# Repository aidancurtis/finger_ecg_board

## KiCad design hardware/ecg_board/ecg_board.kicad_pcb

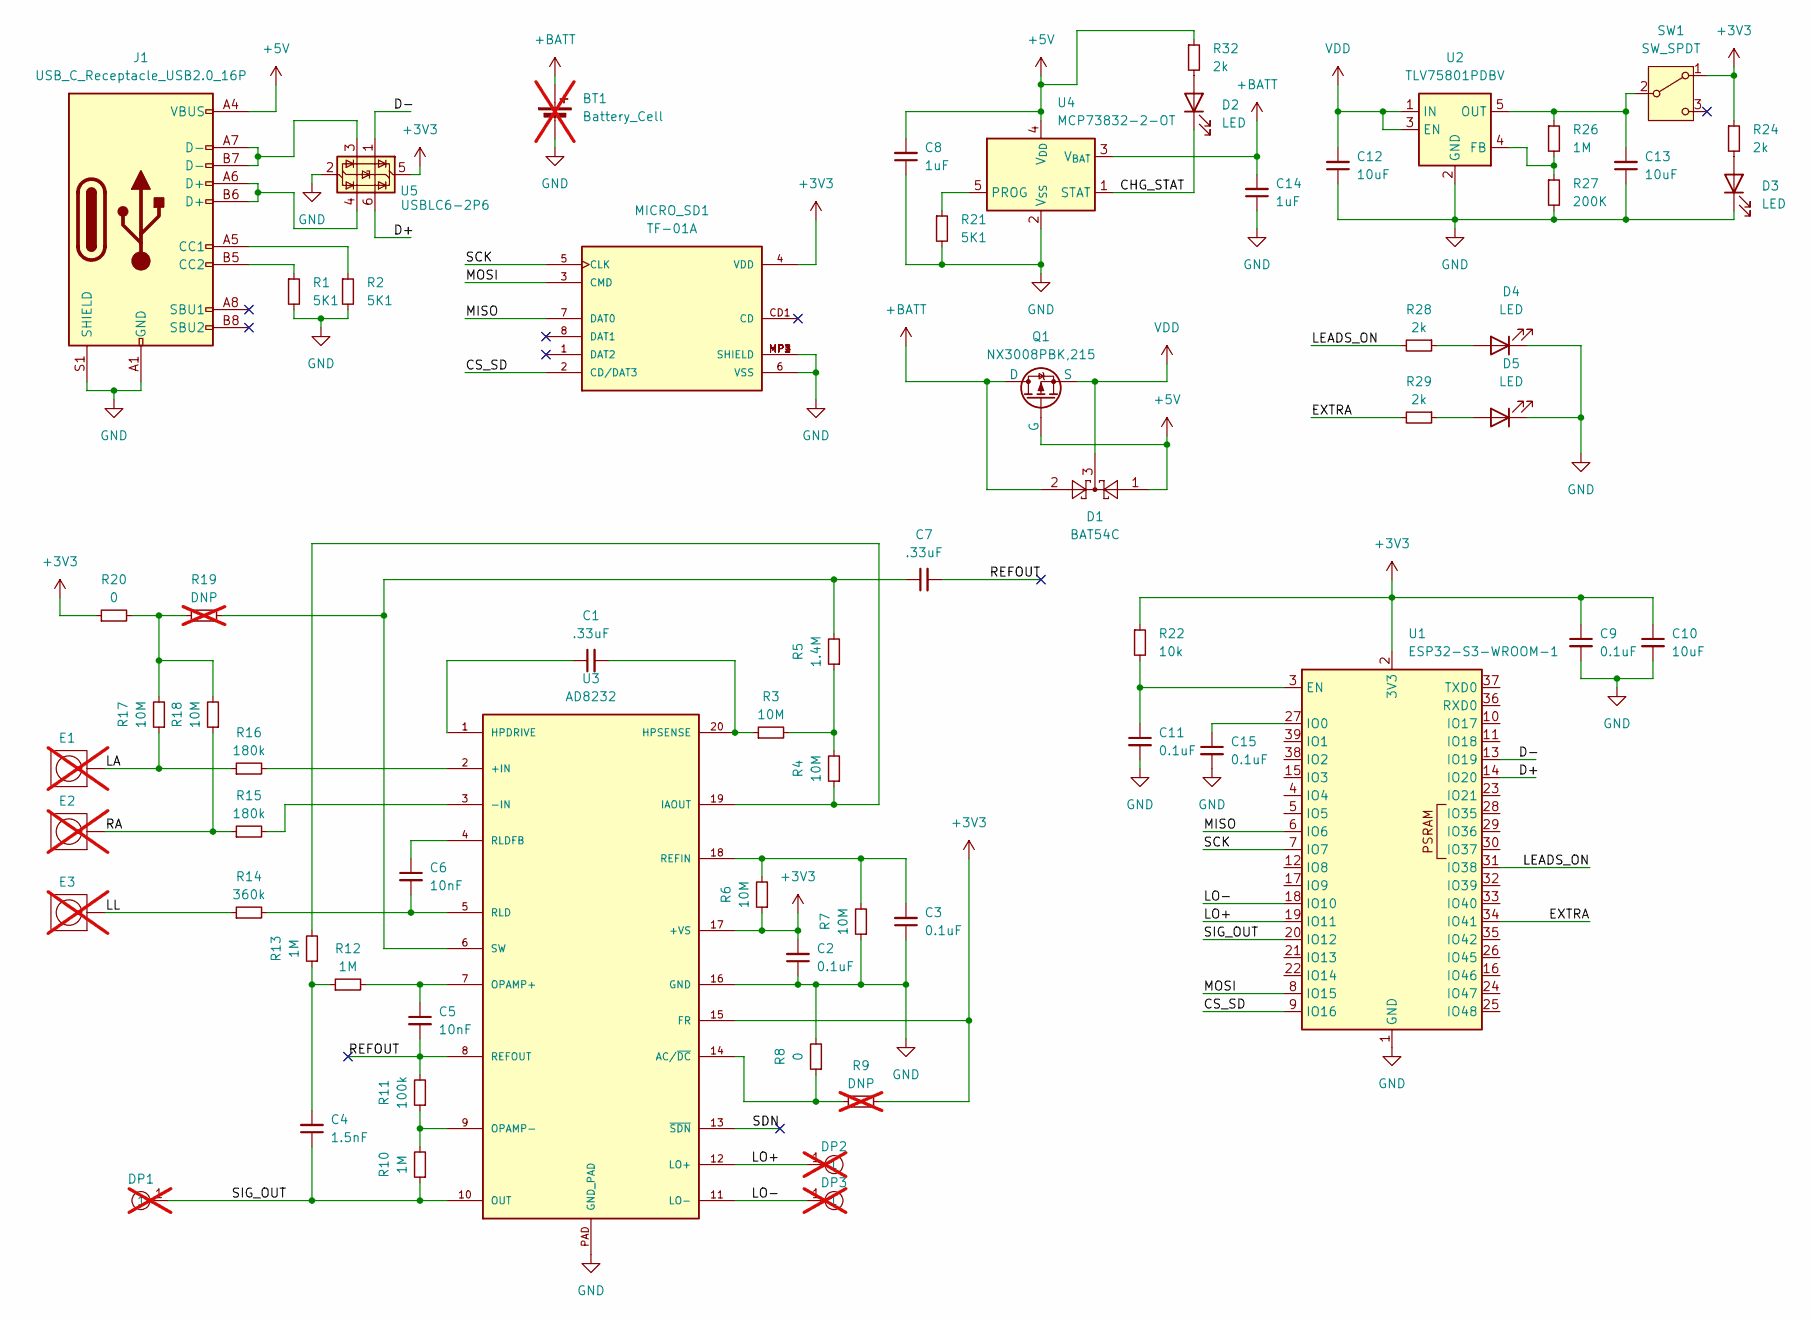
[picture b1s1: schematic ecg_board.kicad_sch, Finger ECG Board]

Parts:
BT1: Battery_Cell; battery_pads; not fitted
C1, C7: .33uF; C_0603_1608Metric; LCSC Part # C2991452
C2, C3, C9, C11, C15: 0.1uF; C_0603_1608Metric; LCSC Part # C14663
C4: 1.5nF; C_0603_1608Metric; LCSC Part # C1588
C5, C6: 10nF; C_0603_1608Metric; LCSC Part # C57112
C8, C14: 1uF; C_0603_1608Metric; LCSC Part # C15849
C10, C12, C13: 10uF; C_0805_2012Metric; LCSC Part # C19702
D1: BAT54C; SOT-23; LCSC Part # C2828464
D2, D3, D4: LED; LED_0603_1608Metric; LCSC Part # C2286
D5: LED; LED_0603_1608Metric; LCSC Part # C5123548
DP1, DP2, DP3: DebugPad; not fitted
E1, E2, E3: Finger_Electrode; not fitted
J1: USB_C_Receptacle_USB2.0_16P; USB_C_Receptacle_HCTL_HC-TYPE-C-16P-01A; LCSC Part # C2927038
MICRO_SD1: TF-01A; LCSC Part # C2889258
Q1: NX3008PBK,215; SOT-23-3; LCSC Part # C131670
R1, R2, R21: 5K1; R_0603_1608Metric; LCSC Part # C23186
R3, R4, R6, R7, R17, R18: 10M; R_0603_1608Metric; LCSC Part # C7250
R5: 1.4M; R_0603_1608Metric; LCSC Part # C3016282
R8, R20: 0; R_0603_1608Metric; LCSC Part # C21189
R9, R19: DNP; R_0603_1608Metric; not fitted
R10, R12, R13, R26: 1M; R_0603_1608Metric; LCSC Part # C22935
R11: 100k; R_0603_1608Metric; LCSC Part # C25803
R14: 360k; R_0603_1608Metric; LCSC Part # C3016408
R15, R16: 180k; R_0603_1608Metric; LCSC Part # C325602
R22: 10k; R_0603_1608Metric; LCSC Part # C25804
R24, R28, R29, R32: 2k; R_0603_1608Metric; LCSC Part # C22975
R27: 200K; R_0603_1608Metric; LCSC Part # C25811
SW1: SW_SPDT; SW_SPDT_PCM12; LCSC Part # C109335
U1: ESP32-S3-WROOM-1; LCSC Part # C2913197
U2: TLV75801PDBV; SOT-23-5; LCSC Part # C2877852
U3: AD8232; LFCSP_20; LCSC Part # C43216
U4: MCP73832-2-OT; SOT-23-5; LCSC Part # C38066
U5: USBLC6-2P6; SOT-666; LCSC Part # C2827693

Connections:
+3V3: C2.2, C9.1, C10.1, MICRO_SD1.4 (VDD), R6.1, R9.2, R20.1, R22.1, R24.1, SW1.1 (A), U1.2 (3V3), U3.15 (FR), U3.17 (+VS), U5.5 (VBUS)
+5V: C8.2, D1.1, J1.A4 (VBUS), J1.A9 (VBUS), J1.B4 (VBUS), J1.B9 (VBUS), Q1.2 (G), R32.1, U4.4 (V_{DD})
+BATT: BT1.1 (+), C14.2, D1.2, Q1.1 (D), U4.3 (V_{BAT})
/CHG_STAT: D2.1 (K), U4.1 (STAT)
/CS_SD: MICRO_SD1.2 (CD/DAT3), U1.9 (IO16)
/D+: U1.14 (IO20), U5.6 (I/O1)
/D-: U1.13 (IO19), U5.1 (I/O1)
/EXTRA: R29.2, U1.34 (IO41)
/LA: E1.1, R16.1, R17.1
/LEADS_ON: R28.2, U1.31 (IO38)
/LL: E3.1, R14.1
/LO+: DP2.1, U1.19 (IO11), U3.12 (LO+); also elsewhere on the board
/LO-: DP3.1, U1.18 (IO10), U3.11 (LO-); also elsewhere on the board
/MISO: MICRO_SD1.7 (DAT0), U1.6 (IO6)
/MOSI: MICRO_SD1.3 (CMD), U1.8 (IO15)
/RA: E2.1, R15.1, R18.1
/REFOUT: C5.2, C7.2, R11.2, U3.8 (REFOUT)
/SCK: MICRO_SD1.5 (CLK), U1.7 (IO7)
/SDN: U3.13 (~SDN)
/SIG_OUT: C4.1, DP1.1, R10.1, U1.20 (IO12), U3.10 (OUT); also elsewhere on the board
GND: BT1.2 (-), C2.1, C3.1, C8.1, C9.2, C10.2, C11.2, C12.1, C13.1, C14.1, C15.2, D3.1 (K), D4.1 (K), D5.1 (K), J1.A1 (GND), J1.A12 (GND), J1.B1 (GND), J1.B12 (GND), J1.S1 (SHIELD), MICRO_SD1.6 (VSS), MICRO_SD1.MP1 (SHIELD), MICRO_SD1.MP2 (SHIELD), MICRO_SD1.MP3 (SHIELD), MICRO_SD1.MP4 (SHIELD), R1.2, R2.2, R7.1, R8.2, R21.2, R27.2, U1.1 (GND), U1.40 (GND), U1.41 (GND), U2.2 (GND), U3.16 (GND), U3.PAD (GND_PAD), U4.2 (V_{SS}), U5.2 (GND)
unnamed: C4.2, R12.1, R13.1
unnamed: D2.2 (A), R32.2
unnamed: D3.2 (A), R24.2
unnamed: D4.2 (A), R28.1
unnamed: D5.2 (A), R29.1
unnamed: J1.A5 (CC1), R2.1
unnamed: J1.B5 (CC2), R1.1
unnamed: J1.A6 (D+), J1.B6 (D+), U5.4 (I/O2)
unnamed: J1.A7 (D-), J1.B7 (D-), U5.3 (I/O2)
unnamed: R3.2, R4.2, R5.1
unnamed: R17.2, R18.2, R19.1, R20.2
unnamed: C13.2, R26.1, SW1.2 (B), U2.5 (OUT)
unnamed: C11.1, R22.2, U1.3 (EN)
unnamed: C15.1, U1.27 (IO0)
unnamed: R26.2, R27.1, U2.4 (FB)
unnamed: R16.2, U3.2 (+IN)
unnamed: R15.2, U3.3 (-IN)
unnamed: R8.1, R9.1, U3.14 (AC/~DC)
unnamed 39: C1.1, U3.1 (HPDRIVE); also elsewhere on the board
unnamed 40: C1.2, R3.1, U3.20 (HPSENSE); also elsewhere on the board
unnamed: R4.1, R13.2, U3.19 (IAOUT)
unnamed: C5.1, R12.2, U3.7 (OPAMP+)
unnamed: R10.2, R11.1, U3.9 (OPAMP-)
unnamed: C3.2, R6.2, R7.2, U3.18 (REFIN)
unnamed: C6.2, R14.2, U3.5 (RLD)
unnamed: C6.1, U3.4 (RLDFB)
unnamed: C7.1, R5.2, R19.2, U3.6 (SW)
unnamed: R21.1, U4.5 (PROG)
VDD: C12.2, D1.3, Q1.3 (S), U2.1 (IN), U2.3 (EN)

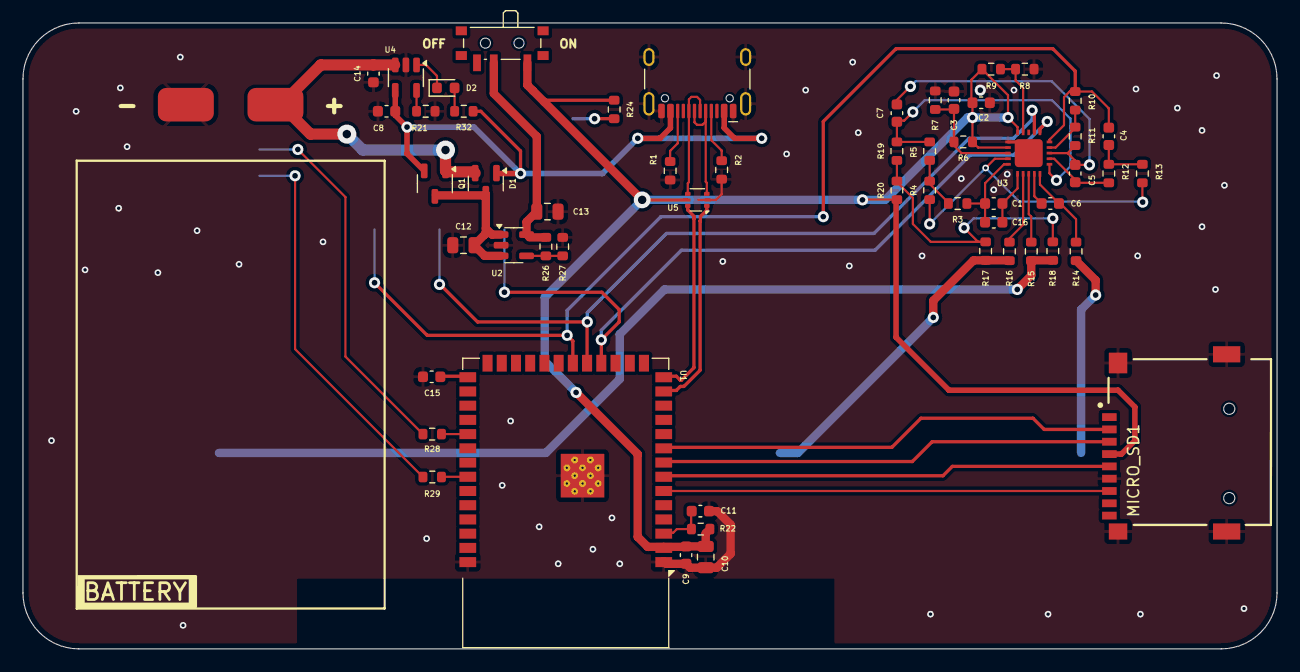
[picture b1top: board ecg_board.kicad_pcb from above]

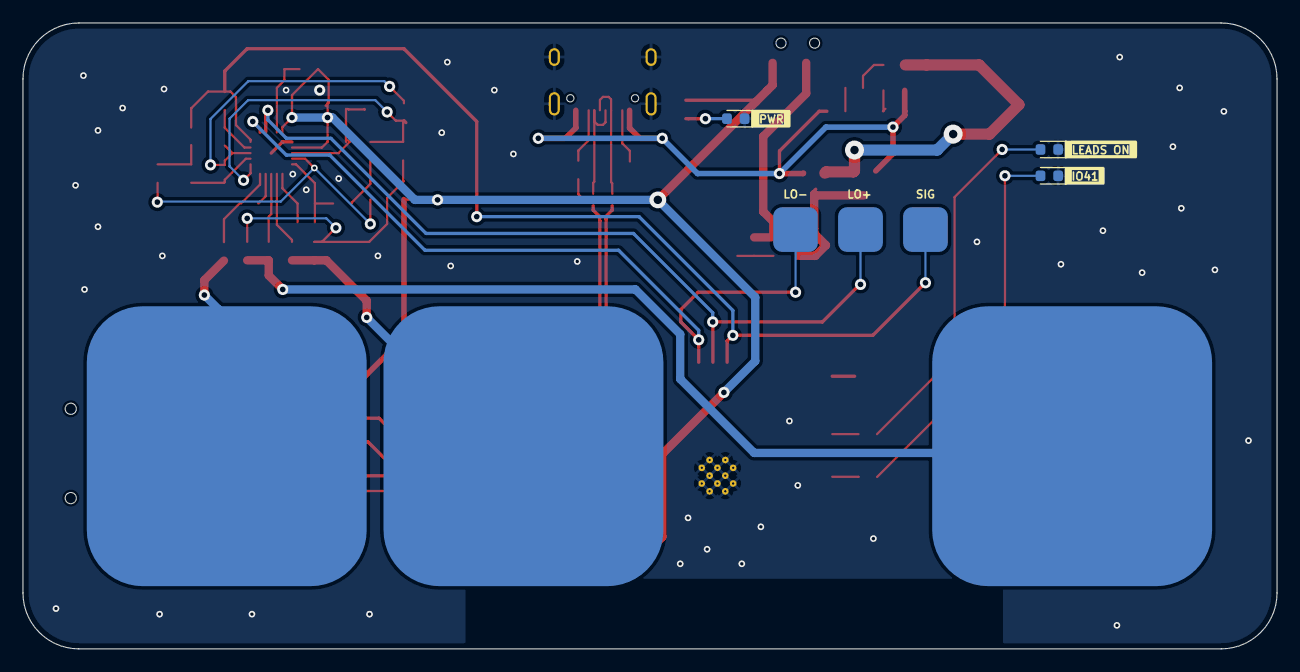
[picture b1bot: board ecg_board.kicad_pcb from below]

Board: 2 copper layers, 112.0 x 55.9 mm, 65 parts (9 on the bottom side), 49 nets.

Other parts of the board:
C16: 220nF; C_0603_1608Metric
LO+: DebugPad
LO-: DebugPad
SIG: DebugPad

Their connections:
/LO+: LO+.1; also elsewhere on the board
/LO-: LO-.1; also elsewhere on the board
/SIG_OUT: SIG.1; also elsewhere on the board
unnamed 39: C16.1; also elsewhere on the board
unnamed 40: C16.2; also elsewhere on the board

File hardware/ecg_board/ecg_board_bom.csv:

"Reference","Value","Datasheet","Footprint","Qty","DNP","LCSC Part #"
"C1",".33uF","~","Capacitor_SMD:C_0603_1608Metric","1","","C2991452"
"C2","0.1uF","~","Capacitor_SMD:C_0603_1608Metric","1","","C14663"
"C3","0.1uF","~","Capacitor_SMD:C_0603_1608Metric","1","","C14663"
"C4","1.5nF","~","Capacitor_SMD:C_0603_1608Metric","1","","C1588"
"C5","10nF","~","Capacitor_SMD:C_0603_1608Metric","1","","C57112"
"C6","10nF","~","Capacitor_SMD:C_0603_1608Metric","1","","C57112"
"C7",".33uF","~","Capacitor_SMD:C_0603_1608Metric","1","","C2991452"
"C8","1uF","~","Capacitor_SMD:C_0603_1608Metric","1","","C15849"
"C9","0.1uF","~","Capacitor_SMD:C_0603_1608Metric","1","","C14663"
"C10","10uF","~","Capacitor_SMD:C_0805_2012Metric","1","","C19702"
"C11","0.1uF","~","Capacitor_SMD:C_0603_1608Metric","1","","C14663"
"C12","10uF","~","Capacitor_SMD:C_0805_2012Metric","1","","C19702"
"C13","10uF","~","Capacitor_SMD:C_0805_2012Metric","1","","C19702"
"C14","1uF","~","Capacitor_SMD:C_0603_1608Metric","1","","C15849"
"C15","0.1uF","~","Capacitor_SMD:C_0603_1608Metric","1","","C14663"
"D1","BAT54C","http://www.diodes.com/_files/datasheets/ds11005.pdf","Package_TO_SOT_SMD:SOT-23","1","","C2828464"
"D2","LED","~","LED_SMD:LED_0603_1608Metric","1","","C2286"
"D3","LED","~","LED_SMD:LED_0603_1608Metric","1","","C2286"
"D4","LED","~","LED_SMD:LED_0603_1608Metric","1","","C2286"
"D5","LED","~","LED_SMD:LED_0603_1608Metric","1","","C5123548"
"J1","USB_C_Receptacle_USB2.0_16P","https://www.usb.org/sites/default/files/documents/usb_type-c.zip","Connector_USB:USB_C_Receptacle_HCTL_HC-TYPE-C-16P-01A","1","","C2927038"
"MICRO_SD1","TF-01A","","TF-01A:TF-01A","1","","C2889258"
"Q1","NX3008PBK,215","https://ngspice.sourceforge.io/docs/ngspice-html-manual/manu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","Package_TO_SOT_SMD:SOT-23-3","1","","C131670"
"R1","5K1","~","Resistor_SMD:R_0603_1608Metric","1","","C23186"
"R2","5K1","~","Resistor_SMD:R_0603_1608Metric","1","","C23186"
"R3","10M","~","Resistor_SMD:R_0603_1608Metric","1","","C7250"
"R4","10M","~","Resistor_SMD:R_0603_1608Metric","1","","C7250"
"R5","1.4M","~","Resistor_SMD:R_0603_1608Metric","1","","C3016282"
"R6","10M","~","Resistor_SMD:R_0603_1608Metric","1","","C7250"
"R7","10M","~","Resistor_SMD:R_0603_1608Metric","1","","C7250"
"R8","0","~","Resistor_SMD:R_0603_1608Metric","1","","C21189"
"R10","1M","~","Resistor_SMD:R_0603_1608Metric","1","","C22935"
"R11","100k","~","Resistor_SMD:R_0603_1608Metric","1","","C25803"
"R12","1M","~","Resistor_SMD:R_0603_1608Metric","1","","C22935"
"R13","1M","~","Resistor_SMD:R_0603_1608Metric","1","","C22935"
"R14","360k","~","Resistor_SMD:R_0603_1608Metric","1","","C3016408"
"R15","180k","~","Resistor_SMD:R_0603_1608Metric","1","","C325602"
"R16","180k","~","Resistor_SMD:R_0603_1608Metric","1","","C325602"
"R17","10M","~","Resistor_SMD:R_0603_1608Metric","1","","C7250"
"R18","10M","~","Resistor_SMD:R_0603_1608Metric","1","","C7250"
"R20","0","~","Resistor_SMD:R_0603_1608Metric","1","","C21189"
"R21","5K1","~","Resistor_SMD:R_0603_1608Metric","1","","C23186"
"R22","10k","~","Resistor_SMD:R_0603_1608Metric","1","","C25804"
"R24","2k","~","Resistor_SMD:R_0603_1608Metric","1","","C22975"
"R26","1M","~","Resistor_SMD:R_0603_1608Metric","1","","C22935"
"R27","200K","~","Resistor_SMD:R_0603_1608Metric","1","","C25811"
"R28","2k","~","Resistor_SMD:R_0603_1608Metric","1","","C22975"
"R29","2k","~","Resistor_SMD:R_0603_1608Metric","1","","C22975"
"R32","2k","~","Resistor_SMD:R_0603_1608Metric","1","","C22975"
"SW1","SW_SPDT","~","Button_Switch_SMD:SW_SPDT_PCM12","1","","C109335"
"U1","ESP32-S3-WROOM-1","https://www.espressif.com/sites/default/files/documentation/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","RF_Module:ESP32-S3-WROOM-1","1","","C2913197"
"U2","TLV75801PDBV","https://www.ti.com/lit/ds/symlink/tlv758p.pdf","Package_TO_SOT_SMD:SOT-23-5","1","","C2877852"
"U3","AD8232","","AD8232:LFCSP_20","1","","C43216"
"U4","MCP73832-2-OT","http://ww1.microchip.com/downloads/en/DeviceDoc/20001984g.pdf","Package_TO_SOT_SMD:SOT-23-5","1","","C38066"
"U5","USBLC6-2P6","https://www.st.com/resource/en/datasheet/usblc6-2.pdf","Package_TO_SOT_SMD:SOT-666","1","","C2827693"

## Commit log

2024-03-16 finished schematic v1
2024-03-22 updated schematic and finish pcb v1
2024-03-25 added components and created bom
2024-03-29 moved switch and fixed bom
2024-04-04 added debugging pads
